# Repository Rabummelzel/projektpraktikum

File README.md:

# Project work at MPIK
You can find my IPython notebook in the protokoll folder.  
To work with the notebook you need to install the following python packages with (may need pip first): 
```
pip3 install jupyter numpy scipy plotly
```
and then run
```
jupyter notebook
```
and select the ipynb file inside the protokoll folder.

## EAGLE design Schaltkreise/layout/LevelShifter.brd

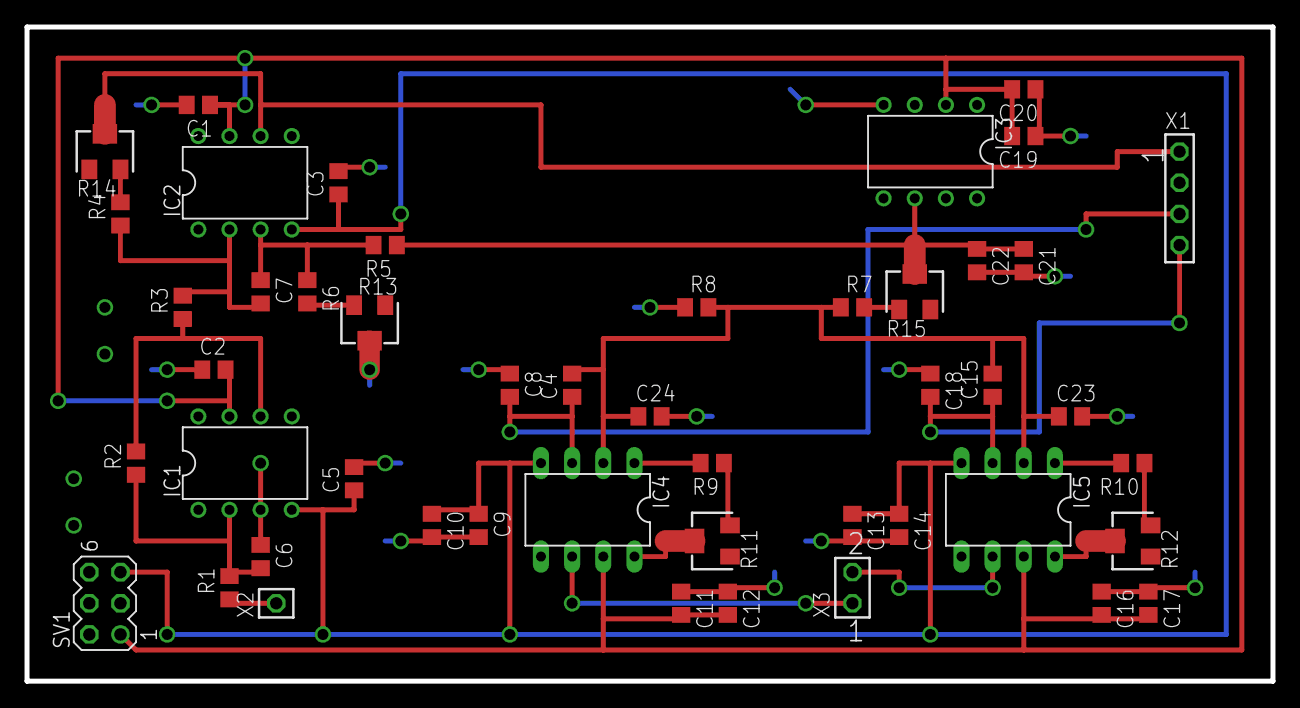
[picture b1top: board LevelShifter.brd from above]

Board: 2 copper layers, 101.6 x 53.3 mm, 48 parts (0 on the bottom side), 24 nets.

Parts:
C1, C2, C3, C4, C5, C6, C7, C8, C9, C10, C11, C12, C13, C14, C15, C16, C17, C18, C19, C20, C21, C22, C23, C24: C0805
IC1, IC2: OP07CN; DIL08
IC3: REF03Z; DIL08
IC4, IC5: AD620N; DIL08
R1, R3, R4, R5, R6, R7, R8, R9, R10: R0805
R2: 133k; R0805
R11, R12, R13, R14, R15: SM-42/43W
SV1: MA03-2
X1: SSW-104-02-S-S
X2: SSW-101-02-S-S
X3: SSW-101-02-S-D

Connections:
+15V: C1.1, C2.2, C11.2, C12.2, C16.2, C17.2, C19.2, C20.2, IC1.7, IC2.7, IC3.2, IC4.7, IC5.7, SV1.1
-15V: C3.1, C5.1, C9.1, C10.1, C13.1, C14.1, IC1.4, IC2.4, IC4.4, IC5.4, SV1.5
GND: C1.2, C2.1, C3.2, C5.2, C6.1, C8.1, C9.2, C10.2, C11.1, C12.1, C13.2, C14.2, C16.1, C17.1, C18.1, C19.1, C20.1, C21.2, C22.2, C23.2, C24.2, IC1.3, IC3.4, R8.1, R13.2, SV1.3, SV1.4, X1.2
unnamed: C6.2, IC1.2, R1.2, R2.1
unnamed: C4.1, C8.2, IC4.3, X1.3
unnamed: IC1.6, R2.2, R3.1
unnamed: C7.2, IC2.2, R3.2, R4.1
unnamed: C7.1, IC2.3, R5.2, R6.1
unnamed: C21.1, C22.1, IC3.6, R5.1, R15.2
unnamed: IC4.8, R11.2
unnamed: R9.1, R11.3
unnamed: IC4.1, R9.2
unnamed: IC5.1, R10.2
unnamed: R7.2, R15.1
unnamed: IC5.8, R12.2
unnamed: C15.1, C18.2, IC5.3, X1.4
unnamed: C4.2, C15.2, C23.1, C24.1, IC4.2, IC5.2, R7.1, R8.2
unnamed: R10.1, R12.3
unnamed: R4.2, R14.3
unnamed: R6.2, R13.3
unnamed: R1.1, X2.1
unnamed: IC4.6, X3.1
unnamed: IC5.6, X3.2
unnamed: IC2.6, R14.2, X1.1

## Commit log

2017-02-22 ¨initial¨
2017-02-22 ¨ẗest¨
2017-02-22 ¨test¨
2017-02-22 ¨newnotebook¨
2017-02-22 remove unnec file
2017-02-22 remove unwanted files
2017-02-22 repair
2017-02-22 test
2017-02-22 remtest
2017-02-22 clean
2017-02-22 update ipynb
2017-02-28 sync
2017-02-28 clean up
2017-03-01 update notebook
2017-03-02 add new image
2017-03-02 sync nb
2017-03-02 create html
2017-03-02 make latex
2017-03-03 add howto.txt
2017-03-03 sync tex
2017-03-08 finish up
2017-03-13 small correction
2017-03-13 add addThee.py
